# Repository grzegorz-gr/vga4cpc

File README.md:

# vga4cpc
VGA output for Amstrad CPC based on Raspberry Pi Pico.<br /> <br />

The goal of this project was to build a scandoubler for Amstrad CPC that is cheap, simple to build and can handle the most popular tricks that Amstrad software does (e.g. smooth scroll) that standard scandoublers usually don't support.
It should work with most LCD monitors. It supports 50.08 FPS to make animations look smoother, but there is also an option to use 60 FPS, if your monitor does not support low frequencies.

Please keep in mind that I am a beginner in electronics, so I could make some serious mistakes. Use it on your own risk.

## Short demo
[https://youtu.be/5xjjsLVpjv0]

## How to build it
Gerber files are in "gerber" directory. I used them with JLCPCB. <br /><br />
Parts:<br />
|Symbol|Value|Quantity|Link|
|---|---|---|---|
|U1|Raspberry Pi Pico|1|[https://www.digikey.com/en/products/detail/raspberry-pi/SC0915/13624793]|
|U2-U4|TLV3202 voltage comparators|3|[https://www.digikey.com/en/products/detail/texas-instruments/TLV3202AIDR/3518740]|
|J1|VGA Socket|1|[https://www.digikey.com/en/products/detail/assmann-wsw-components/A-HDF15A-KG-TAXB/1241905] (Actually it did not fit perfectly, but it was possible to mount it)|
|C1-C9|0.1u ceramic capacitors|9|[https://www.digikey.com/en/products/detail/kyocera-avx/SR215C104JAR/2208907]|
|R1-R3|47 ohm resistors|3|[https://www.digikey.com/en/products/detail/stackpole-electronics-inc/RNMF14FTC47R0/2617352]|
|R4,R14|100 ohm resistors|2|[https://www.digikey.com/en/products/detail/yageo/MFR-25FRF52-100R/14795]|
|R5,R12|1 kOhm resistors|2|[https://www.digikey.com/en/products/detail/yageo/MFR-25FRF52-1K/14891]|
|R6-R11|220 Ohm resistors|6||[https://www.digikey.com/en/products/detail/stackpole-electronics-inc/RNMF14FTC220R/2617314]|
|R13|68 Ohm resistor|1|[https://www.digikey.com/en/products/detail/stackpole-electronics-inc/RNMF14FTC68R0/2617372]|
|R15|22 Ohm resistor|1|[https://www.digikey.com/en/products/detail/yageo/MFR-25FTE52-15R/9139795]|
|R16-R18|75 Ohm resistors|3|[https://www.digikey.com/en/products/detail/yageo/MFR-25FBF52-75R/12771]|
|SW1|50/60 FPS switch|1|[https://www.digikey.com/en/products/detail/c-k/OS102011MA1QS1/1981431]|
|SW2|Reset button|1|[https://www.digikey.com/en/products/detail/te-connectivity-alcoswitch-switches/1-1825027-1/1632544]|
|J2|CPC connection header|1|Just install whatever you need to connect to CPC. I used pin headers and soldered cables to them|
||Din 6 or Din 5 plug (center pin is not used) to connect it to Amstrad unless you plan to solder it directly to PCB|1||

<br /><br />
I wanted to make it easy to solder so almost all parts are TH. Raspberry Pi Pico and comparators are SMD (there was no TH option), but they are quite big and they are simple to solder even without a microscope.
<br /><br />
You need to connect it to Amstrad video port using J2 connector. The pins are: 1 - blue, 2 - green, 3 - red, 4 - GND, 5 - csync. You can connect din-6/din-5 plug there, or solder directly to Amstrad PCB.
<br /><br />
After (or before) building the PCB you just need to upload the software to RPI Pico. Connect it with USB cable to PC/Mac, keeping the small button on Pico board pressed. It should mount as a storage device. Just copy uf2 file there. Pico should unmount and restart then.

## How to use it
Connect 5V power adapter (or just cable to USB port in pc) to RPI Pico. Connect VGA cable to monitor. You can connect the board to Amstrad, but don't turn it on yet. You should see test screen with Amstrad palette on top, some potentially problematic patterns on bottom and 4 squares in corners. Make sure it looks OK. In case of any issues you can try to reset the board with SW2 button. It is also a good moment to try switching the V frequency with SW1 button. If 50.08hz works with your monitor, then use it. In other case, try 60Hz. If squares in corners are not fully visible (the image is shifted), try using Auto-adjust in your monitor.<br />
If everything looks OK, turn on your Amstrad and have fun.<br />

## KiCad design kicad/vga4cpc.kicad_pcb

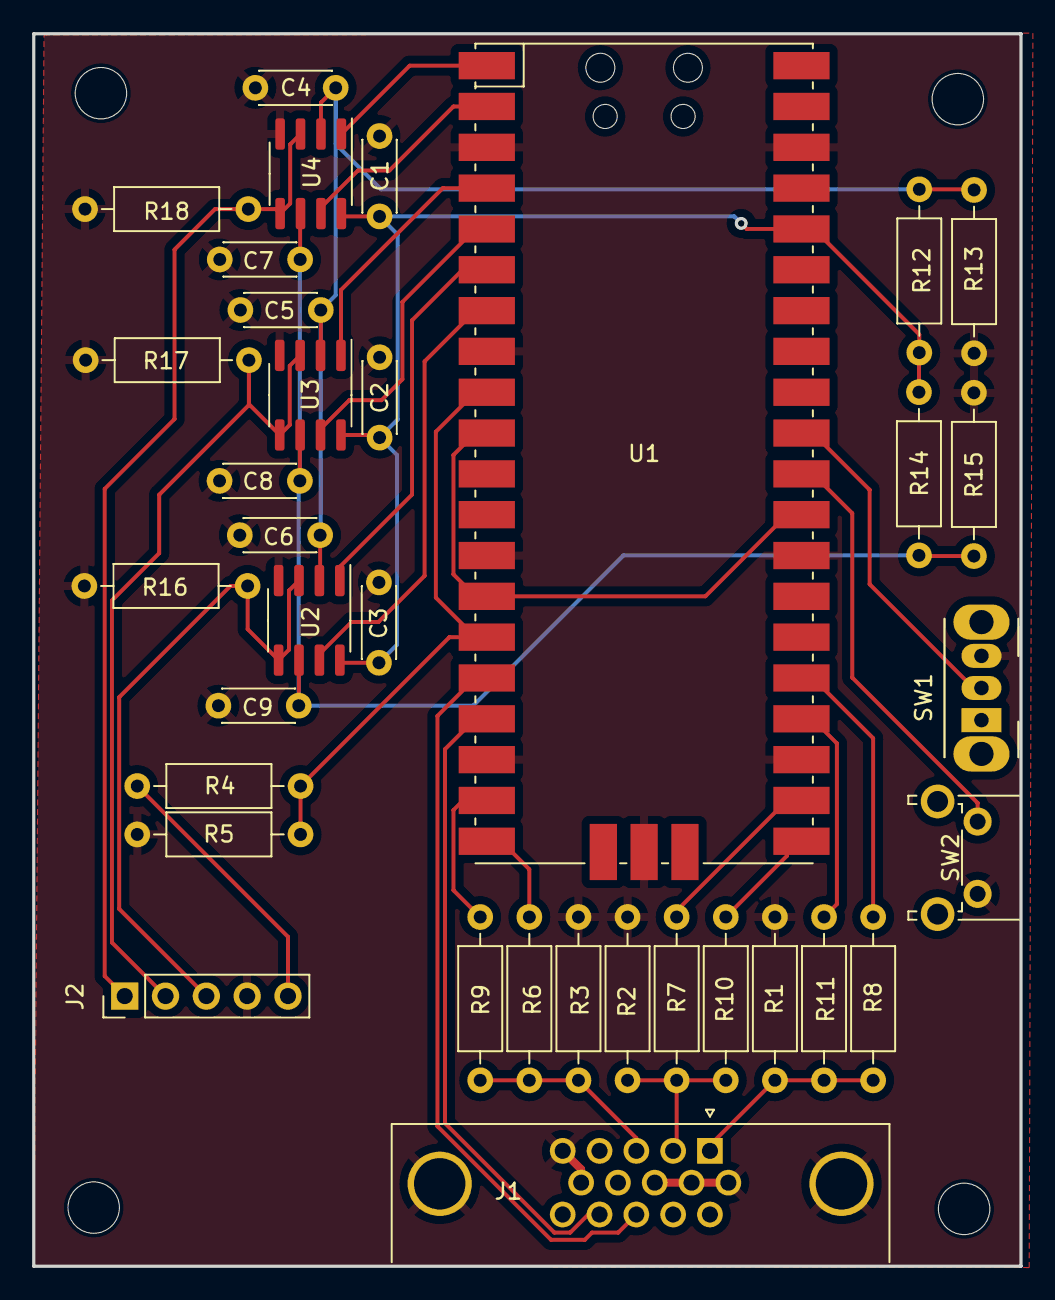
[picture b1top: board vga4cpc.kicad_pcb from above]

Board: 2 copper layers, 61.4 x 76.7 mm, 39 parts (0 on the bottom side), 29 nets.

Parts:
C1, C2, C3, C4, C5, C6, C7, C8, C9: 0.1u; C_Disc_D4.3mm_W1.9mm_P5.00mm
H1, H2, H3, H4: MountingHole; MountingHole_3.2mm_M3
J1: VGA socket; DSUB-15-HD_Female_Horizontal_P2.29x1.98mm_EdgePinOffset3.03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
J2: CPC video port; PinHeader_1x05_P2.54mm_Vertical
R1, R2, R3: 47; R_Axial_DIN0207_L6.3mm_D2.5mm_P10.16mm_Horizontal
R4, R14: 100; R_Axial_DIN0207_L6.3mm_D2.5mm_P10.16mm_Horizontal
R5, R12: 1k; R_Axial_DIN0207_L6.3mm_D2.5mm_P10.16mm_Horizontal
R6, R7, R8, R9, R10, R11: 220; R_Axial_DIN0207_L6.3mm_D2.5mm_P10.16mm_Horizontal
R13: 68; R_Axial_DIN0207_L6.3mm_D2.5mm_P10.16mm_Horizontal
R15: 15; R_Axial_DIN0207_L6.3mm_D2.5mm_P10.16mm_Horizontal
R16, R17, R18: 75; R_Axial_DIN0207_L6.3mm_D2.5mm_P10.16mm_Horizontal
SW1: VFreq sw; SW_CuK_OS102011MA1QN1_SPDT_Angled
SW2: reset; SW_Tactile_SPST_Angled_PTS645Vx31-2LFS
U1: Pico; RPi_Pico_SMD_TH
U2, U3, U4: SOIC-8_3.9x4.9mm_P1.27mm

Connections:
200mV: C4.1, C5.1, C6.1, R12.2, R13.1, U2.2 (1IN-), U3.2 (1IN-), U4.2 (1IN-)
430mV: C7.1, C8.1, C9.1, R14.2, R15.1, U2.6 (2IN-), U3.6 (2IN-), U4.6 (2IN-)
+3.3V: C1.1, C2.1, C3.1, R12.1, R14.1, U1.36 (3V3), U2.8 (Vcc), U3.8 (Vcc), U4.8 (Vcc)
/Comparators/B0: U1.1 (GPIO0), U4.1 (1OUT)
/Comparators/B1: U1.2 (GPIO1), U4.7 (2OUT)
/Comparators/CPC_B: J2.1, R18.1, U4.3 (1IN+), U4.5 (2IN+)
/Comparators/CPC_G: J2.2, R17.1, U3.3 (1IN+), U3.5 (2IN+)
/Comparators/CPC_R: J2.3, R16.1, U2.3 (1IN+), U2.5 (2IN+)
/Comparators/G0: U1.4 (GPIO2), U3.1 (1OUT)
/Comparators/G1: U1.5 (GPIO3), U3.7 (2OUT)
/Comparators/R0: U1.6 (GPIO4), U2.1 (1OUT)
/Comparators/R1: U1.7 (GPIO5), U2.7 (2OUT)
/Connectors/CPC_CSYNC: J2.5, R4.1
/Connectors/VGA_B: J1.3, R3.1, R6.2, R9.2
/Connectors/VGA_G: J1.2, R2.1, R7.2, R10.2
/Connectors/VGA_HSYNC: J1.13, U1.16 (GPIO12)
/Connectors/VGA_R: J1.1, R1.1, R8.2, R11.2
/Connectors/VGA_VSYNC: J1.14, U1.17 (GPIO13)
CSYNC: R4.2, R5.1, U1.9 (GPIO6), U1.15 (GPIO11)
GND: C1.2, C2.2, C3.2, C4.2, C5.2, C6.2, C7.2, C8.2, C9.2, J1.0, J1.5, J1.6, J1.7, J1.8, J1.10, J2.4, R1.2, R2.2, R3.2, R5.2, R13.2, R15.2, R16.2, R17.2, R18.2, SW1.3 (C), SW2.2 (B), U1.3 (GND), U1.8 (GND), U1.13 (GND), U1.18 (GND), U1.23 (GND), U1.28 (GND), U1.38 (GND), U1.42 (GND), U2.4 (GND), U3.4 (GND), U4.4 (GND)
INT_VSYNC: U1.10 (GPIO7), U1.14 (GPIO10), U1.29 (GPIO22)
unnamed: SW1.2 (B), U1.31 (GPIO26_ADC0)
unnamed: SW2.1 (A), U1.30 (RUN)
unnamed: R9.1, U1.19 (GPIO14)
unnamed: R6.1, U1.20 (GPIO15)
unnamed: R10.1, U1.21 (GPIO16)
unnamed: R7.1, U1.22 (GPIO17)
unnamed: R11.1, U1.24 (GPIO18)
unnamed: R8.1, U1.25 (GPIO19)

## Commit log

2024-06-11 uf2 file added
2024-06-12 Schematics draft pdf
2024-07-03 Bugfix in csync analysis (Fixes Edge Grinder) and a couple more
2024-07-15 A couple bugs fixed
2024-07-21 Schematics, gerbers, kicad
2024-07-21 clean up
2024-07-22 board photo
2024-10-28 fixed uf2 file
